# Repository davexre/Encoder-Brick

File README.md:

# Encoder-Brick
 
 This is a small board that implements a typical quadrature encoder. It includes provisions for hardware debouncing the A/B
 pins on the encoder. It also can optionally support a click button built into the encoder unit, too.

 ## Debouncing circuit
 
 Two of these circuits are on the board. Note that the "internal" resistor indicated is the internal pin PULLUP resistor
 on an Arduino-ish board. If your intended use case doesn't have internal pullups, you might need to add resistors to make
 this circuit work.

```
      (internal 20k)       10k
 pin:<---/\/\--------*----/\/\----|
                     |            |
              0.1uf ===            / switch
                     |            /
 gnd:<---------------*------------|
 ```
 
 ## Bill of Materials
 
 - [encoder](https://www.mouser.com/ProductDetail/Bourns/PEC11R-4215F-S0024?qs=Zq5ylnUbLm5lAqmKF80wzQ%3D%3D)
 - [a 4 pin header/connector with .1" pitch](https://www.mouser.com/ProductDetail/molex/22-23-2042/?qs=52ipEG6BoUGnVIQV2y3Jgg%3D%3D&countrycode=US&currencycode=USD)
 - 2x 10k axial lead resistors (whatever you have on hand should work)
 - 2x [0.1uF ceramic capacitor](https://www.mouser.com/ProductDetail/Vishay-BC-Components/K104K15X7RF53H5?qs=sGAEpiMZZMuMW9TJLBQkXpsARSeHIOPdD%2FiGrRofazY%3D) (again, whatever you have with the right value should work)
 
 Any quadrature encoder with the same footprint will work - there are a bunch, with various shaft lengths and styles!
 You may also want a knob.

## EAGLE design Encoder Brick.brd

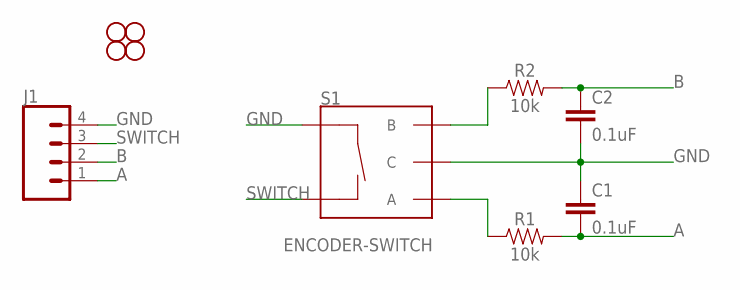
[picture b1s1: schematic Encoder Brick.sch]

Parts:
C1, C2: 0.1uF; CAP-PTH-SMALL-KIT
J1: CONN_04POLAR; MOLEX-1X4
JP3, JP4, JP11, JP13: STAND-OFF
R1, R2: 10k; AXIAL-0.3-KIT
S1: ENCODER-SWITCH; ROTARY_ENC_PLAIN

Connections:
A: C1.2, J1.1, R1.P$2 (2)
B: C2.1, J1.2, R2.P$2 (2)
GND: C1.1, C2.2, J1.4, S1.C, S1.SW+
unnamed: R2.P$1 (1), S1.B
unnamed: R1.P$1 (1), S1.A
SWITCH: J1.3, S1.SW-

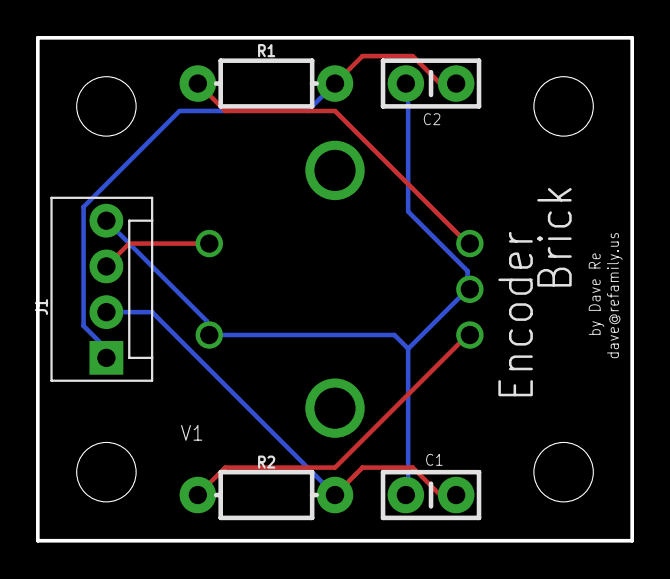
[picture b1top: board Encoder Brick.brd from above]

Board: 2 copper layers, 33.0 x 27.9 mm, 10 parts (1 on the bottom side), 6 nets.

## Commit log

2020-05-26 Initial commit
    Rev v1.0 of the Encoder Brick

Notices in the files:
parts and their libraries:
SparkFun-Capacitors: Licensing: Creative Commons ShareAlike 4.0 International - https://creativecommons.org/licenses/by-sa/4.0
